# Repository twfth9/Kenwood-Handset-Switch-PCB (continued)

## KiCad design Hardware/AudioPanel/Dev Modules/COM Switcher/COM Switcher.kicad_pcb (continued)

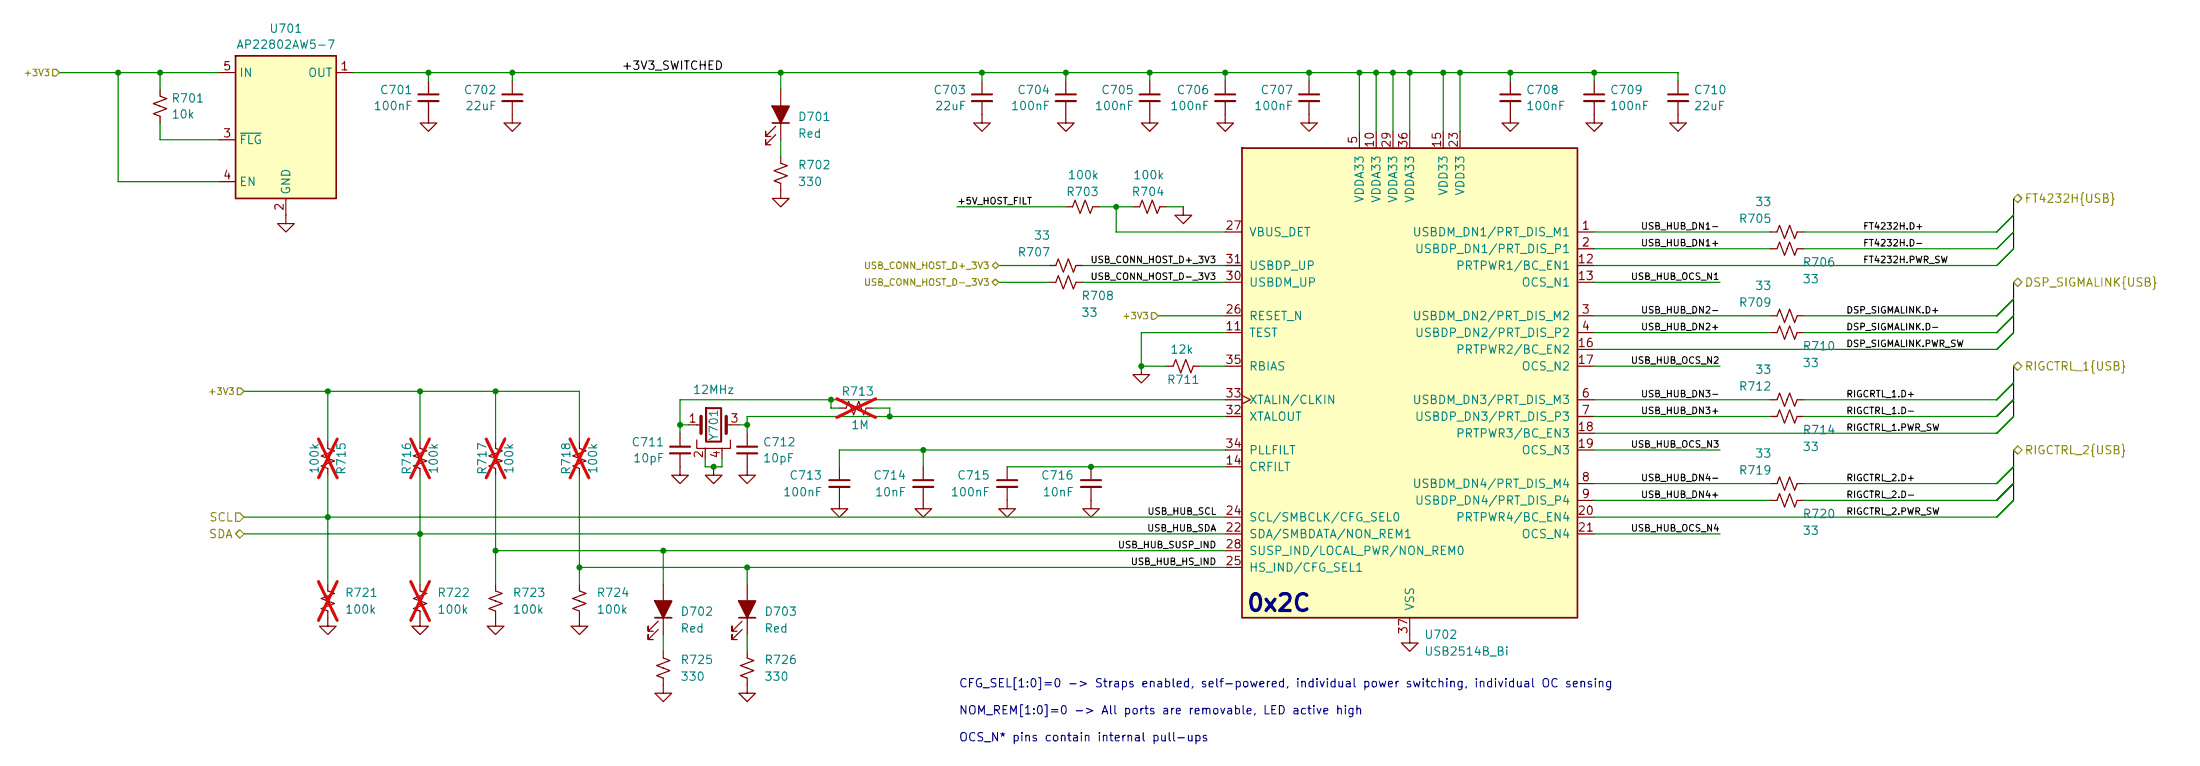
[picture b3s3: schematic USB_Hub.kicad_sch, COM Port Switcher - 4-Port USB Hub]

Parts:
C701, C704, C705, C706, C707, C708, C709, C713, C715: 100nF; Worthington_C_0402
C702, C703, C710: 22uF; Worthington_C_0603
C711, C712: 10pF; Worthington_C_0402
C714, C716: 10nF; Worthington_C_0402
D701, D702, D703: Red; Worthington_LED_0603; DigiKey Part Number 732-5016-ND
R701: 10k; Worthington_R_0402
R702, R725, R726: 330; Worthington_R_0402; DigiKey Part Number 311-510HRCT-ND
R703, R704, R723, R724: 100k; Worthington_R_0402
R705, R706, R707, R708, R709, R710, R712, R714, R719, R720: 33; Worthington_R_0402
R711: 12k; Worthington_R_0402
R713: 1M; Worthington_R_0402; not fitted
R715, R716, R717, R718, R721, R722: 100k; Worthington_R_0402; not fitted
U701: AP22802AW5-7; SC-74A-5_1.55x2.9mm_P0.95mm
U702: USB2514B_Bi; QFN-36-1EP_6x6mm_P0.5mm_EP3.7x3.7mm
Y701: 12MHz; Crystal_SMD_Abracon_ABM8AIG-4Pin_3.2x2.5mm

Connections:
/+3V3_USB2514: R701.1, R715.2, R716.1, R717.1, R718.1, U701.4 (EN), U701.5 (IN), U702.26 (RESET_N); also elsewhere on the board
/FT4232H/FT4232H.D+: R705.2; also elsewhere on the board
/FT4232H/FT4232H.D-: R706.1; also elsewhere on the board
/FT4232H/FT4232H.PWR_SW: U702.12 (PRTPWR1/BC_EN1)
/SAMD_SCL: R715.1, R721.1, U702.24 (SCL/SMBCLK/CFG_SEL0)
/SAMD_SDA: R716.2, R722.1, U702.22 (SDA/SMBDATA/NON_REM1)
/USB Hub/+3V3_SWITCHED: C701.1, C702.1, C703.1, C704.1, C705.1, C706.1, C707.1, C708.1, C709.1, C710.1, D701.2 (A), U701.1 (OUT), U702.5 (VDDA33), U702.10 (VDDA33), U702.15 (VDD33), U702.23 (VDD33), U702.29 (VDDA33), U702.36 (VDDA33)
/USB Hub/+5V_HOST_FILT: R703.1
/USB Hub/DSP_SIGMALINK.D+: R709.2; also elsewhere on the board
/USB Hub/DSP_SIGMALINK.D-: R710.1; also elsewhere on the board
/USB Hub/DSP_SIGMALINK.PWR_SW: U702.16 (PRTPWR2/BC_EN2); also elsewhere on the board
/USB Hub/RIGCRTL_1.D+: R712.2
/USB Hub/RIGCTRL_1.D-: R714.1; also elsewhere on the board
/USB Hub/RIGCTRL_1.PWR_SW: U702.18 (PRTPWR3/BC_EN3); also elsewhere on the board
/USB Hub/RIGCTRL_2.D+: R719.2; also elsewhere on the board
/USB Hub/RIGCTRL_2.D-: R720.1; also elsewhere on the board
/USB Hub/RIGCTRL_2.PWR_SW: U702.20 (PRTPWR4/BC_EN4); also elsewhere on the board
/USB Hub/USB_HUB_DN1+: R706.2, U702.2 (USBDP_DN1/PRT_DIS_P1)
/USB Hub/USB_HUB_DN1-: R705.1, U702.1 (USBDM_DN1/PRT_DIS_M1)
/USB Hub/USB_HUB_DN2+: R710.2, U702.4 (USBDP_DN2/PRT_DIS_P2)
/USB Hub/USB_HUB_DN2-: R709.1, U702.3 (USBDM_DN2/PRT_DIS_M2)
/USB Hub/USB_HUB_DN3+: R714.2, U702.7 (USBDP_DN3/PRT_DIS_P3)
/USB Hub/USB_HUB_DN3-: R712.1, U702.6 (USBDM_DN3/PRT_DIS_M3)
/USB Hub/USB_HUB_DN4+: R720.2, U702.9 (USBDP_DN4/PRT_DIS_P4)
/USB Hub/USB_HUB_DN4-: R719.1, U702.8 (USBDM_DN4/PRT_DIS_M4)
/USB Hub/USB_HUB_HS_IND: D703.2 (A), R718.2, R724.1, U702.25 (HS_IND/CFG_SEL1)
/USB Hub/USB_HUB_OCS_N1: U702.13 (OCS_N1)
/USB Hub/USB_HUB_OCS_N2: U702.17 (OCS_N2)
/USB Hub/USB_HUB_OCS_N3: U702.19 (OCS_N3)
/USB Hub/USB_HUB_OCS_N4: U702.21 (OCS_N4)
/USB Hub/USB_HUB_SUSP_IND: D702.2 (A), R717.2, R723.1, U702.28 (SUSP_IND/LOCAL_PWR/NON_REM0)
/USBHUB_HOST_D+: R707.1, R707.2, U702.31 (USBDP_UP); also elsewhere on the board
/USBHUB_HOST_D-: R708.1, R708.2, U702.30 (USBDM_UP); also elsewhere on the board
GND: C701.2, C702.2, C703.2, C704.2, C705.2, C706.2, C707.2, C708.2, C709.2, C710.2, C711.2, C712.2, C713.2, C714.2, C715.2, C716.2, R702.1, R704.2, R711.2, R721.2, R722.2, R723.2, R724.2, R725.1, R726.1, U701.2 (GND), U702.11 (TEST), U702.37 (VSS), Y701.2, Y701.4; also elsewhere on the board
unnamed: D701.1 (K), R702.2
unnamed: D702.1 (K), R725.2
unnamed: D703.1 (K), R726.2
unnamed: R701.2, U701.3 (~FLG)
unnamed: C715.1, C716.1, U702.14 (CRFILT)
unnamed: C713.1, C714.1, U702.34 (PLLFILT)
unnamed: R711.1, U702.35 (RBIAS)
unnamed: R703.2, R704.1, U702.27 (VBUS_DET)
unnamed: C711.1, R713.1, U702.33 (XTALIN/CLKIN), Y701.1
unnamed: C712.1, R713.2, U702.32 (XTALOUT), Y701.3

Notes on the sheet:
0x2C
CFG_SEL[1:0]=0 -> Straps enabled, self-powered, individual power switching, individual OC sensing NOM_REM[1:0]=0 -> All ports are removable, LED active high OCS_N* pins contain internal pull-ups

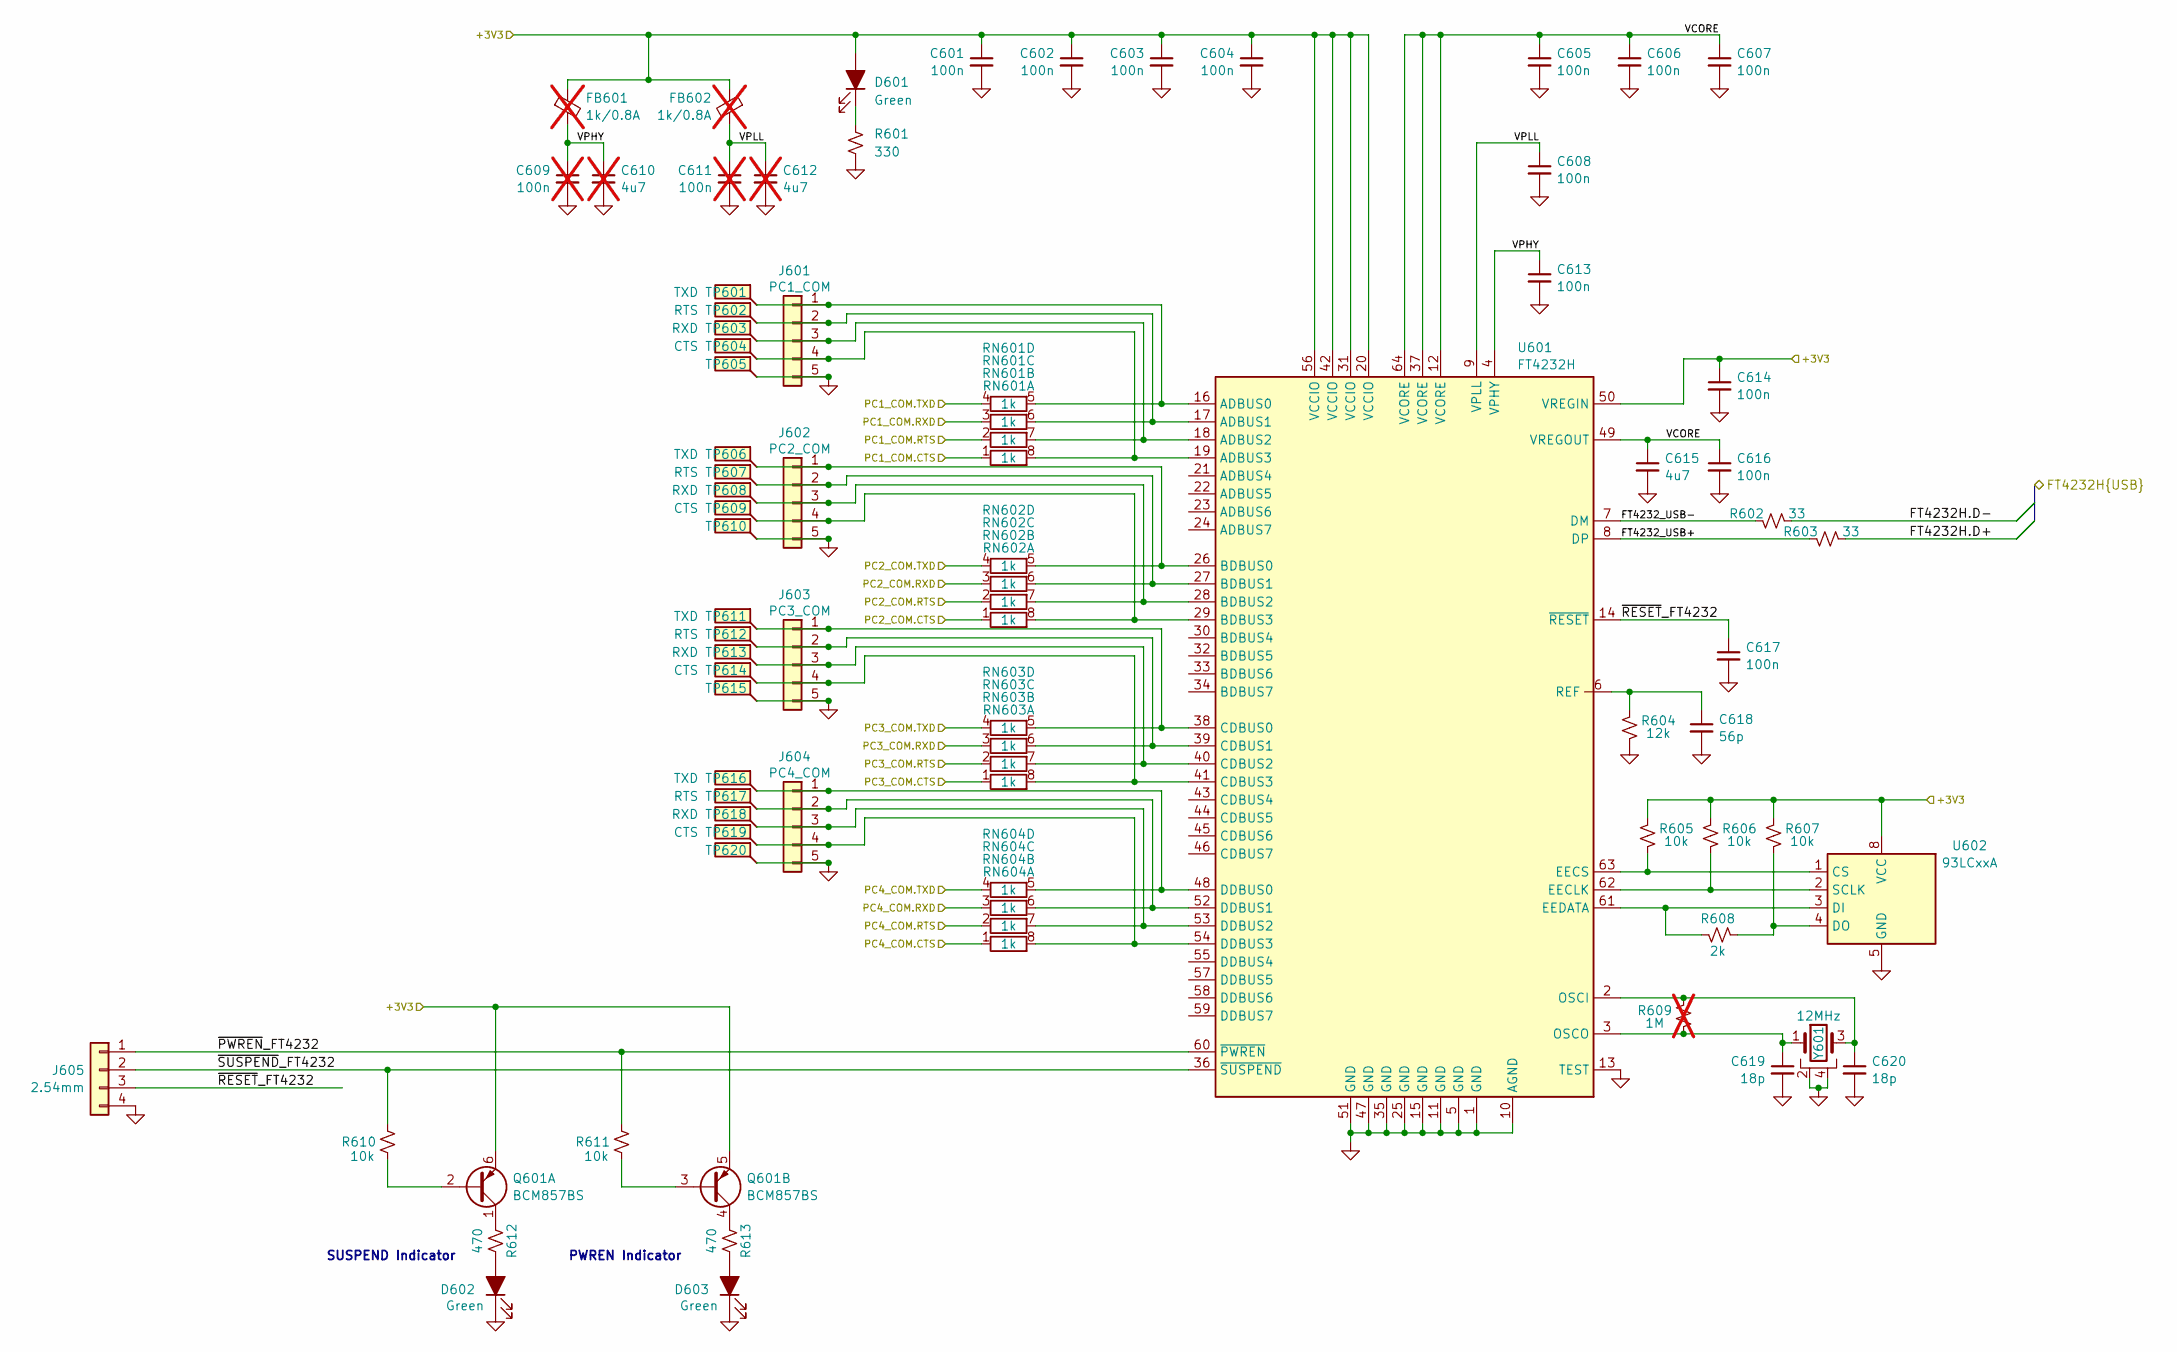
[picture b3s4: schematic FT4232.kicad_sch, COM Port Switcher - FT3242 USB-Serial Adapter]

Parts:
C601, C602, C603, C604, C605, C606, C607, C608, C613, C614, C616, C617: 100n; Worthington_C_0402
C609, C611: 100n; Worthington_C_0402; not fitted
C610: 4u7; Worthington_C_0603; not fitted
C612: 4u7; Worthington_C_0402; not fitted
C615: 4u7; Worthington_C_0603
C618: 56p; Worthington_C_0402
C619, C620: 18p; Worthington_C_0402
D601, D602, D603: Green; Worthington_LED_0603; DigiKey Part Number 732-5016-ND
FB601, FB602: 1k/0.8A; L_1206_3216Metric_Pad1.22x1.90mm_HandSolder; not fitted
J601: PC1_COM; PinHeader_1x05_P2.54mm_Vertical
J602: PC2_COM; PinHeader_1x05_P2.54mm_Vertical
J603: PC3_COM; PinHeader_1x05_P2.54mm_Vertical
J604: PC4_COM; PinHeader_1x05_P2.54mm_Vertical
J605: 2.54mm; PinHeader_1x04_P2.54mm_Vertical
Q601: BCM857BS; SOT-363_SC-70-6
R601: 330; Worthington_R_0402; DigiKey Part Number 311-510HRCT-ND
R602, R603: 33; Worthington_R_0402
R604: 12k; Worthington_R_0402
R605, R606, R607, R610, R611: 10k; Worthington_R_0402
R608: 2k; Worthington_R_0402
R609: 1M; Worthington_R_0402; not fitted
R612, R613: 470; Worthington_R_0402
RN601, RN602, RN603, RN604: 1k; RES_ARRAY_4RES_0804
TP601, TP606, TP611, TP616: TXD; KEYSTONE_5017
TP602, TP607, TP612, TP617: RTS; KEYSTONE_5017
TP603, TP608, TP613, TP618: RXD; KEYSTONE_5017
TP604, TP609, TP614, TP619: CTS; KEYSTONE_5017
TP605, TP610, TP615, TP620: KEYSTONE_5017
U601: FT4232H; QFN-64-1EP_9x9mm_P0.5mm_EP6x6mm
U602: 93LCxxA; SOIC-8_3.9x4.9mm_P1.27mm
Y601: 12MHz; Crystal_SMD_Abracon_ABM8AIG-4Pin_3.2x2.5mm

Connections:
/+3V3_FT4232: C601.1, C602.1, C603.1, C604.1, C614.1, D601.2 (A), FB601.1, FB602.1, Q601.5 (E2), Q601.6 (E1), R605.1, R606.1, R607.1, U601.20 (VCCIO), U601.31 (VCCIO), U601.42 (VCCIO), U601.50 (VREGIN), U601.56 (VCCIO), U602.8 (VCC); also elsewhere on the board
/FT4232H/FT4232H.D+: R603.2; also elsewhere on the board
/FT4232H/FT4232H.D-: R602.2; also elsewhere on the board
/FT4232H/FT4232_USB+: R603.1, U601.8 (DP)
/FT4232H/FT4232_USB-: R602.1, U601.7 (DM)
/FT4232H/VCORE: C605.1, C606.1, C607.1, C615.1, C616.1, U601.12 (VCORE), U601.37 (VCORE), U601.49 (VREGOUT), U601.64 (VCORE)
/FT4232H/VPHY: C609.1, C610.1, C613.1, FB601.2, U601.4 (VPHY)
/FT4232H/VPLL: C608.1, C611.1, C612.1, FB602.2, U601.9 (VPLL)
/FT4232H/~PWREN_FT4232: J605.1, R611.1, U601.60 (~PWREN)
/FT4232H/~RESET_FT4232: C617.1, J605.3, U601.14 (~RESET)
/FT4232H/~SUSPEND_FT4232: J605.2, R610.1, U601.36 (~SUSPEND)
/PC1_COM.CTS: RN601.1 (4); also elsewhere on the board
/PC1_COM.RTS: RN601.2; also elsewhere on the board
/PC1_COM.RX: RN601.3; also elsewhere on the board
/PC1_COM.TX: RN601.4; also elsewhere on the board
/PC2_COM.CTS: RN602.1 (4); also elsewhere on the board
/PC2_COM.RTS: RN602.2; also elsewhere on the board
/PC2_COM.RX: RN602.3; also elsewhere on the board
/PC2_COM.TX: RN602.4; also elsewhere on the board
/PC3_COM.CTS: RN603.1 (4); also elsewhere on the board
/PC3_COM.RTS: RN603.2; also elsewhere on the board
/PC3_COM.RX: RN603.3; also elsewhere on the board
/PC3_COM.TX: RN603.4; also elsewhere on the board
/PC4_COM.CTS: RN604.1 (4); also elsewhere on the board
/PC4_COM.RTS: RN604.2; also elsewhere on the board
/PC4_COM.RX: RN604.3; also elsewhere on the board
/PC4_COM.TX: RN604.4; also elsewhere on the board
GND: C601.2, C602.2, C603.2, C604.2, C605.2, C606.2, C607.2, C608.2, C609.2, C610.2, C611.2, C612.2, C613.2, C614.2, C615.2, C616.2, C617.2, C618.2, C619.2, C620.2, D602.1 (K), D603.1 (K), J601.5, J602.5, J603.5, J604.5, J605.4, R601.1, R604.2, TP605.1, TP610.1, TP615.1, TP620.1, U601.1 (GND), U601.5 (GND), U601.10 (AGND), U601.11 (GND), U601.13 (TEST), U601.15 (GND), U601.25 (GND), U601.35 (GND), U601.47 (GND), U601.51 (GND), U601.65 (GND), U602.5 (GND), Y601.2, Y601.4; also elsewhere on the board
unnamed: D601.1 (K), R601.2
unnamed: D602.2 (A), R612.1
unnamed: D603.2 (A), R613.1
unnamed: J601.1, RN601.5, TP601.1, U601.16 (ADBUS0)
unnamed: J601.2, RN601.6, TP602.1, U601.17 (ADBUS1)
unnamed: J601.3, RN601.7 (5), TP603.1, U601.18 (ADBUS2)
unnamed: J601.4, RN601.8, TP604.1, U601.19 (ADBUS3)
unnamed: J602.1, RN602.5, TP606.1, U601.26 (BDBUS0)
unnamed: J602.2, RN602.6, TP607.1, U601.27 (BDBUS1)
unnamed: J602.3, RN602.7 (5), TP608.1, U601.28 (BDBUS2)
unnamed: J602.4, RN602.8, TP609.1, U601.29 (BDBUS3)
unnamed: J603.1, RN603.5, TP611.1, U601.38 (CDBUS0)
unnamed: J603.2, RN603.6, TP612.1, U601.39 (CDBUS1)
unnamed: J603.3, RN603.7 (5), TP613.1, U601.40 (CDBUS2)
unnamed: J603.4, RN603.8, TP614.1, U601.41 (CDBUS3)
unnamed: J604.1, RN604.5, TP616.1, U601.48 (DDBUS0)
unnamed: J604.2, RN604.6, TP617.1, U601.52 (DDBUS1)
unnamed: J604.3, RN604.7 (5), TP618.1, U601.53 (DDBUS2)
unnamed: J604.4, RN604.8, TP619.1, U601.54 (DDBUS3)
unnamed: Q601.2 (B1), R610.2
unnamed: Q601.1 (C1), R612.2
unnamed: Q601.3 (B2), R611.2
unnamed: Q601.4 (C2), R613.2
unnamed: R606.2, U601.62 (EECLK), U602.2 (SCLK)
unnamed: R605.2, U601.63 (EECS), U602.1 (CS)
unnamed: R608.1, U601.61 (EEDATA), U602.3 (DI)
unnamed: C620.1, R609.2, U601.2 (OSCI), Y601.3
unnamed: C619.1, R609.1, U601.3 (OSCO), Y601.1
unnamed: C618.1, R604.1, U601.6 (REF)
unnamed: R607.2, R608.2, U602.4 (DO)

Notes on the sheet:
PWREN Indicator
SUSPEND Indicator

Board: 2 copper layers, 459 parts (0 on the bottom side), 317 nets, no tracks yet.

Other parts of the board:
C308, C310: 100p; Worthington_C_0402

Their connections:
/D-710 COM Port Protection/CTS_232_FROM_RADIO_3V3: C310.1; also elsewhere on the board
/D-710 COM Port Protection/GND_232_FROM_RADIO: C308.2, C310.2; also elsewhere on the board
/D-710 COM Port Protection/RTS_232_3V3O_RADIO_3V3: C308.1; also elsewhere on the board

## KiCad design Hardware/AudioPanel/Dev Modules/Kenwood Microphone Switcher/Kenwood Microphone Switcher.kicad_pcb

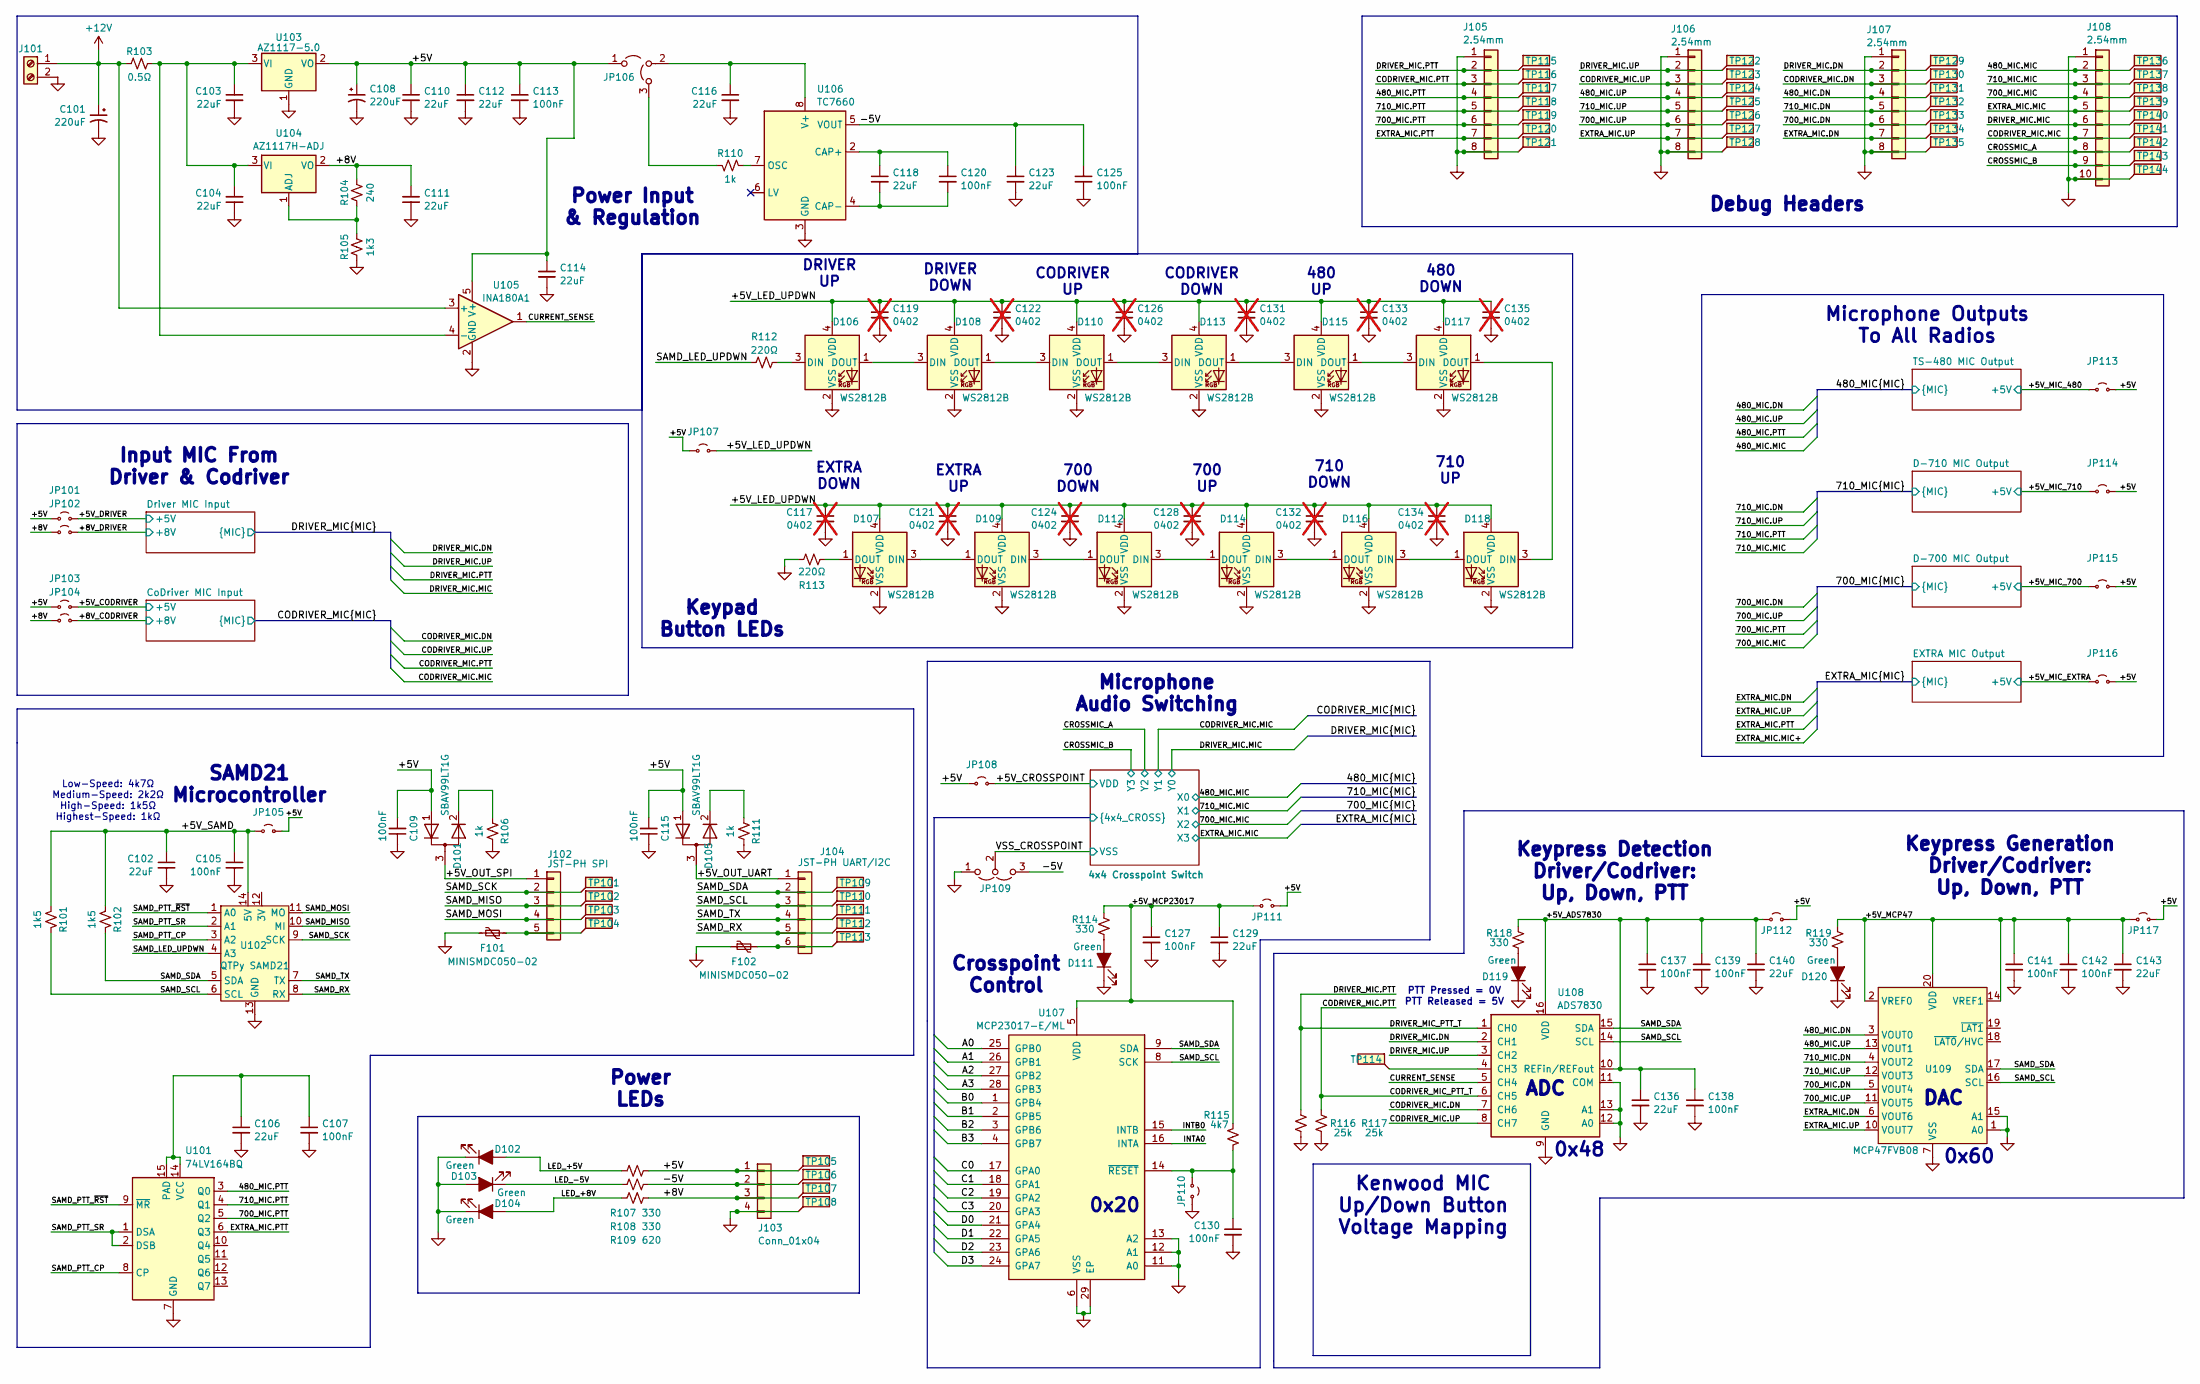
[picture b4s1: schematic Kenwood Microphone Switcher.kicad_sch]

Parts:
C101, C108: 220uF; CP_Elec_10x10
C102, C103, C104, C106, C110, C111, C112, C114, C116, C118, C123, C129, C136, C140, C143: 22uF; C_0603_1608Metric
C105, C107, C109, C113, C115, C120, C125, C127, C130, C137, C138, C139, C141, C142: 100nF; C_0402_1005Metric
C117, C119, C121, C122, C124, C126, C128, C131, C132, C133, C134, C135: 0402; C_0402_1005Metric; not fitted
D101, D105: SBAV99LT1G; SOT-23
D102, D103, D104, D111, D119, D120: Green; LED_0603_1608Metric; DigiKey Part Number 732-5016-ND
D106, D107, D108, D109, D110, D112, D113, D114, D115, D116, D117, D118: WS2812B; LED_WS2812B-2020_PLCC4_2.0x2.0mm
F101, F102: MINISMDC050-02; Fuse_0805_2012Metric
J101: Screw_Terminal_01x02; TerminalBlock_Phoenix_MKDS-1,5-2_1x02_P5.00mm_Horizontal
J102: JST-PH SPI; JST_PH_S5B-PH-K_1x05_P2.00mm_Horizontal
J103: Conn_01x04; PinHeader_1x04_P2.54mm_Vertical
J104: JST-PH UART/I2C; JST_PH_S6B-PH-K_1x06_P2.00mm_Horizontal
J105, J106, J107: 2.54mm; PinHeader_1x08_P2.54mm_Vertical
J108: 2.54mm; PinHeader_1x10_P2.54mm_Vertical
JP101, JP102, JP103, JP104, JP105, JP107, JP108, JP110, JP111, JP112, JP113, JP114, JP115, JP116, JP117: Jumper_2_Small_Open; SolderJumper-2_P1.3mm_Open_Pad1.0x1.5mm
JP106, JP109: Jumper_3_Open; SolderBridge_3L
R101, R102: 1k5; R_0402_1005Metric
R103: 0.5Ω; R_0402_1005Metric
R104: 240; R_0402_1005Metric
R105: 1k3; R_0402_1005Metric
R106, R110, R111: 1k; R_0402_1005Metric
R107, R108, R114, R118, R119: 330; R_0402_1005Metric
R109: 620; R_0402_1005Metric
R112, R113: 220Ω; R_0402_1005Metric
R115: 4k7; R_0402_1005Metric
R116, R117: 25k; R_0402_1005Metric
TP101, TP102, TP103, TP104, TP105, TP106, TP107, TP108, TP109, TP110, TP111, TP112, TP113, TP114, TP115, TP116, TP117, TP118, TP119, TP120, TP121, TP122, TP123, TP124, TP125, TP126, TP127, TP128, TP129, TP130, TP131, TP132, TP133, TP134, TP135, TP136, TP137, TP138, TP139, TP140, TP141, TP142, TP143, TP144: TestPoint_Flag; KEYSTONE_5017
U101: 74LV164BQ; DHVQFN-14-1EP_2.5x3mm_P0.5mm_EP1x1.5mm
U102: QTPy SAMD21; Py_QT_SAMD21
U103: AZ1117-5.0; SOT-223-3_TabPin2
U104: AZ1117H-ADJ; SOT-223-3_TabPin2
U105: INA180A1; SOT-23-5
U106: TC7660; SOIC-8_3.9x4.9mm_P1.27mm
U107: MCP23017-E/ML; QFN-28-1EP_6x6mm_P0.65mm_EP4.25x4.25mm
U108: ADS7830; TSSOP-16_4.4x5mm_P0.65mm
U109: MCP47FVB08; QFN-20-5x5

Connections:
+12V: C101.1, J101.1, R103.2, U105.3 (+)
/4x4 Crosspoint Switch/A0: U107.25 (GPB0); also elsewhere on the board
/4x4 Crosspoint Switch/A1: U107.26 (GPB1); also elsewhere on the board
/4x4 Crosspoint Switch/A2: U107.27 (GPB2); also elsewhere on the board
/4x4 Crosspoint Switch/A3: U107.28 (GPB3); also elsewhere on the board
/4x4 Crosspoint Switch/B0: U107.1 (GPB4); also elsewhere on the board
/4x4 Crosspoint Switch/B1: U107.2 (GPB5); also elsewhere on the board
/4x4 Crosspoint Switch/B2: U107.3 (GPB6); also elsewhere on the board
/4x4 Crosspoint Switch/B3: U107.4 (GPB7); also elsewhere on the board
/4x4 Crosspoint Switch/C0: U107.17 (GPA0); also elsewhere on the board
/4x4 Crosspoint Switch/C1: U107.18 (GPA1); also elsewhere on the board
/4x4 Crosspoint Switch/C2: U107.19 (GPA2); also elsewhere on the board
/4x4 Crosspoint Switch/C3: U107.20 (GPA3); also elsewhere on the board
/4x4 Crosspoint Switch/D0: U107.21 (GPA4); also elsewhere on the board
/4x4 Crosspoint Switch/D1: U107.22 (GPA5); also elsewhere on the board
/4x4 Crosspoint Switch/D2: U107.23 (GPA6); also elsewhere on the board
/4x4 Crosspoint Switch/D3: U107.24 (GPA7); also elsewhere on the board
/480_MIC.DN: J107.4, TP131.1, U109.3 (VOUT0)
/480_MIC.MIC: J108.2, TP136.1; also elsewhere on the board
/480_MIC.PTT: J105.4, TP117.1, U101.3 (Q0); also elsewhere on the board
/480_MIC.UP: J106.4, TP124.1, U109.13 (VOUT1); also elsewhere on the board
/700_MIC.DN: J107.6, TP133.1, U109.5 (VOUT4)
/700_MIC.MIC: J108.4, TP138.1; also elsewhere on the board
/700_MIC.PTT: J105.6, TP119.1, U101.5 (Q2); also elsewhere on the board
/700_MIC.UP: J106.6, TP126.1, U109.11 (VOUT5); also elsewhere on the board
/710_MIC.DN: J107.5, TP132.1, U109.4 (VOUT2)
/710_MIC.MIC: J108.3, TP137.1; also elsewhere on the board
/710_MIC.PTT: J105.5, TP118.1, U101.4 (Q1); also elsewhere on the board
/710_MIC.UP: J106.5, TP125.1, U109.12 (VOUT3); also elsewhere on the board
/+5V: C108.1, C109.2, C110.1, C112.1, C113.1, C114.1, C115.2, D101.1 (A), D105.1 (A), J103.1, JP101.1 (A), JP103.1 (A), JP105.1 (A), JP106.1 (A), JP107.1 (A), JP108.1 (A), JP111.2 (B), JP112.2 (B), JP113.1 (A), JP114.1 (A), JP115.1 (A), JP116.1 (A), JP117.2 (B), R107.1, TP105.1, U103.2 (VO), U105.5 (V+)
/+5V_ADS7830: C136.1, C137.1, C138.1, C139.1, C140.1, JP112.1 (A), R118.2, U108.10 (REFin/REFout), U108.16 (VDD)
/+5V_CODRIVER: JP103.2 (B); also elsewhere on the board
/+5V_CROSSPOINT: JP108.2 (B); also elsewhere on the board
/+5V_DRIVER: JP101.2 (B); also elsewhere on the board
/+5V_LED_UPDWN: C117.1, C119.1, C121.1, C122.1, C124.1, C126.1, C128.1, C131.1, C132.1, C133.1, C134.1, C135.1, D106.4 (VDD), D107.4 (VDD), D108.4 (VDD), D109.4 (VDD), D110.4 (VDD), D112.4 (VDD), D113.4 (VDD), D114.4 (VDD), D115.4 (VDD), D116.4 (VDD), D117.4 (VDD), D118.4 (VDD), JP107.2 (B)
/+5V_MCP47: C141.1, C142.1, C143.1, JP117.1 (A), R119.2, U109.2 (VREF0), U109.14 (VREF1), U109.20 (VDD)
/+5V_MCP23017: C127.1, C129.1, JP111.1 (A), R114.2, R115.1, U107.5 (VDD)
/+5V_MIC_480: JP113.2 (B); also elsewhere on the board
/+5V_MIC_700: JP115.2 (B); also elsewhere on the board
/+5V_MIC_710: JP114.2 (B); also elsewhere on the board
/+5V_MIC_EXTRA: JP116.2 (B); also elsewhere on the board
/+5V_OUT_SPI: D101.3 (common), J102.1
/+5V_OUT_UART: D105.3 (common), J104.1
/+5V_SAMD: C102.1, C105.1, JP105.2 (B), R101.1, R102.1, U102.14 (5V)
/+8V: C111.1, J103.3, JP102.1 (A), JP104.1 (A), R104.1, R109.1, TP107.1, U104.2 (VO)
/+8V_CODRIVER: JP104.2 (B); also elsewhere on the board
/+8V_DRIVER: JP102.2 (B); also elsewhere on the board
/-5V: C123.1, C125.1, J103.2, JP109.3 (B), R108.1, TP106.1, U106.5 (VOUT)
/CODRIVER_MIC.DN: J107.3, TP130.1, U108.7 (CH6)
/CODRIVER_MIC.MIC: J108.7, TP141.1; also elsewhere on the board
/CODRIVER_MIC.PTT: J105.3, R117.1, TP116.1, U108.6 (CH5); also elsewhere on the board
/CODRIVER_MIC.UP: J106.3, TP123.1, U108.8 (CH7); also elsewhere on the board
/CROSSMIC_A: J108.8, TP142.1; also elsewhere on the board
/CROSSMIC_B: J108.9, TP143.1; also elsewhere on the board
/CURRENT_SENSE: U105.1, U108.5 (CH4)
/DRIVER_MIC.DN: J107.2, TP129.1, U108.2 (CH1)
/DRIVER_MIC.MIC: J108.6, TP140.1; also elsewhere on the board
/DRIVER_MIC.PTT: J105.2, R116.2, TP115.1, U108.1 (CH0); also elsewhere on the board
/DRIVER_MIC.UP: J106.2, TP122.1, U108.3 (CH2); also elsewhere on the board
/EXTRA_MIC.DN: J107.7, TP134.1, U109.6 (VOUT6)
/EXTRA_MIC.MIC: J108.5, TP139.1; also elsewhere on the board
/EXTRA_MIC.PTT: J105.7, TP120.1, U101.6 (Q3); also elsewhere on the board
/EXTRA_MIC.UP: J106.7, TP127.1, U109.10 (VOUT7); also elsewhere on the board
/INTA0: U107.16 (INTA)
/INTB0: U107.15 (INTB)
/LED_+5V: D102.2 (A), R107.2
/LED_+8V: D104.2 (A), R109.2
/LED_-5V: D103.1 (K), R108.2
/SAMD_LED_UPDWN: R112.1, U102.4 (A3)
/SAMD_MISO: J102.3, TP102.1, U102.10 (MI)
/SAMD_MOSI: J102.4, TP103.1, U102.11 (MO)
/SAMD_PTT_CP: U101.8 (CP), U102.3 (A2)
/SAMD_PTT_SR: U101.1 (DSA), U101.2 (DSB), U102.2 (A1)
/SAMD_PTT_~RST: U101.9 (~MR), U102.1 (A0)
/SAMD_RX: J104.5, TP112.1, U102.8 (RX)
/SAMD_SCK: J102.2, TP101.1, U102.9 (SCK)
/SAMD_SCL: J104.3, R101.2, TP110.1, U102.6 (SCL), U107.8 (SCK), U108.14 (SCL), U109.16 (SCL)
/SAMD_SDA: J104.2, R102.2, TP109.1, U102.5 (SDA), U107.9 (SDA), U108.15 (SDA), U109.17 (SDA)
/SAMD_TX: J104.4, TP111.1, U102.7 (TX)
/VSS_CROSSPOINT: JP109.2 (C); also elsewhere on the board
GND: C101.2, C102.2, C103.2, C104.2, C105.2, C106.2, C107.2, C108.2, C109.1, C110.2, C111.2, C112.2, C113.2, C114.2, C115.1, C116.2, C117.2, C119.2, C121.2, C122.2, C123.2, C124.2, C125.2, C126.2, C127.2, C128.2, C129.2, C130.2, C131.2, C132.2, C133.2, C134.2, C135.2, C136.2, C137.2, C138.2, C139.2, C140.2, C141.2, C142.2, C143.2, D102.1 (K), D103.2 (A), D104.1 (K), D106.2 (VSS), D107.2 (VSS), D108.2 (VSS), D109.2 (VSS), D110.2 (VSS), D111.1 (K), D112.2 (VSS), D113.2 (VSS), D114.2 (VSS), D115.2 (VSS), D116.2 (VSS), D117.2 (VSS), D118.2 (VSS), D119.1 (K), D120.1 (K), F101.1, F102.1, J101.2, J103.4, J105.1, J105.8, J106.1, J106.8, J107.1, J107.8, J108.1, J108.10, JP109.1 (A), JP110.1 (A), R105.2, R106.1, R111.1, R113.2, R116.1, R117.2, TP108.1, TP121.1, TP128.1, TP135.1, TP144.1, U101.7 (GND), U102.13 (GND), U103.1 (GND), U105.2 (GND), U106.3 (GND), U107.6 (VSS), U107.11 (A0), U107.12 (A1), U107.13 (A2), U107.29 (EP), U108.9 (GND), U108.11 (COM), U108.12 (A0), U108.13 (A1), U109.1 (A0), U109.7 (VSS), U109.15 (A1), U109.EP; also elsewhere on the board
unnamed: D101.2 (K), R106.2
unnamed: D105.2 (K), R111.2
unnamed: D106.3 (DIN), R112.2
unnamed: D106.1 (DOUT), D108.3 (DIN)
unnamed: D107.3 (DIN), D109.1 (DOUT)
unnamed: D107.1 (DOUT), R113.1
unnamed: D108.1 (DOUT), D110.3 (DIN)
unnamed: D109.3 (DIN), D112.1 (DOUT)
unnamed: D110.1 (DOUT), D113.3 (DIN)
unnamed: D111.2 (A), R114.1
unnamed: D112.3 (DIN), D114.1 (DOUT)
unnamed: D113.1 (DOUT), D115.3 (DIN)
unnamed: D114.3 (DIN), D116.1 (DOUT)
unnamed: D115.1 (DOUT), D117.3 (DIN)
unnamed: D116.3 (DIN), D118.1 (DOUT)
unnamed: D117.1 (DOUT), D118.3 (DIN)
unnamed: D119.2 (A), R118.1
unnamed: D120.2 (A), R119.1
unnamed: F101.2, J102.5, TP104.1
unnamed: F102.2, J104.6, TP113.1
unnamed: JP106.3 (B), R110.1
unnamed: C116.1, JP106.2 (C), U106.8 (V+)
unnamed: C130.1, JP110.2 (B), R115.2, U107.14 (~RESET)
unnamed: C106.1, C107.1, U101.14 (VCC), U101.15 (PAD)
unnamed: C103.1, C104.1, R103.1, U103.3 (VI), U104.3 (VI), U105.4 (-)
unnamed: R104.2, R105.1, U104.1 (ADJ)
unnamed: C118.1, C120.1, U106.2 (CAP+)
unnamed: C118.2, C120.2, U106.4 (CAP-)
unnamed: R110.2, U106.7 (OSC)
unnamed: TP114.1, U108.4 (CH3)

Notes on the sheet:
0x20
480 UP
0x48
Keypress Generation Driver/Codriver: Up, Down, PTT
700 DOWN
Power Input & Regulation
Microphone Audio Switching
Input MIC From Driver & Codriver
480 DOWN
710 DOWN
DRIVER UP
Kenwood MIC Up/Down Button Voltage Mapping
Microphone Outputs To All Radios
0x60
Keypad Button LEDs
Power LEDs
710 UP
DRIVER DOWN
PTT Pressed = 0V PTT Released = 5V
SAMD21 Microcontroller
Debug Headers
EXTRA DOWN
Low-Speed: 4k7Ω Medium-Speed: 2k2Ω High-Speed: 1k5Ω Highest-Speed: 1kΩ
ADC
CODRIVER DOWN
Keypress Detection Driver/Codriver: Up, Down, PTT
CODRIVER UP
700 UP
Crosspoint Control
DAC
EXTRA UP
